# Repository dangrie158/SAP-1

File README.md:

# SAP-1 (Simple as Possible)

A simple 8-bit micro-processor using mostly discrete logic chips.

This project is mostly based on the [8-bit Breadboard computer](https://eater.net/8bit) by [Ben Eater](https://eater.net)

## Banner Specs

- ~400 Hz Clock
- 8-bit Data Bus
- 16-bit Control Word
- 5 Microsteps per Instruction
- 16 byte RAM

## Documentation

Check the projects [Pages](https://dangrie158.github.io/SAP-1/) for the documentation of the ISA and Hardware modules.

## Submodules:

- Clock with adjustable frequency and single-step button
- 2 8-bit Data Registers (A & B)
- ALU implementing sum and difference between Registers A & B, carry and zero flag
- Flag Register to save the ALU flags between instructions
- 4-bit Instruction Counter with load (jump)
- Output module to display a byte as positive decimal or 2s-complement with data latch
- Random Access Memory with 16 Bytes for instructions and data
- 4-bit Memory Address Register to address the 16 bytes of RAM
- 8-bit Instruction Register with the upper nibble representing the opcode, the lower nibble can be used for instruction parameters
- Instruction Decoder to run the microcode of the 16 different instructions with 5 microinstuctions each. Uses a 16-bit control word to control the other modules

## Project Structure

| Files                           | Description                                                                                   |
|---------------------------------|-----------------------------------------------------------------------------------------------|
| ```Board/Board.*```             | Autodesk Eagle project woth the Schematic and a fully routed Boardlayout                      |
| ```Board/Board_*.zip```         | precreated Gerbers for Production                                                             |
| ```Board/BOM.xlsx```            | a BOM with [Mouser](https://www.mouser.com) partnumbers                                       |
| ```Spec/ISA.py```               | a Python module that defines and documents the Instruction Set Architecture of the Processor. |
| ```Spec/lut_microcode.py```     | script to create the microcode LUT binary for the ID EEPROMS. Uses ```ISA.py```               |
| ```Spec/lut_outputdecoder.py``` | script to create the LUT binary for the output decode EEPROM                                  |
| ```LUTs/*.bin```                | precreated binaries for the EEPROMS                                                           |
| ```Example-Programs/*.s```      | Some Example Programs in SAP-1 assembly                                                       |
| ```Tools/sap-asm```             | Assembler for SAP-1 assembly listings. Outputs binaries or prints programming instructions.   |
| ```Simulations/```              | [iCircuit](http://icircuitapp.com) simulation files for some parts of the architecture        |

## Writing Code
The documentation has an extensive section on the [Instruction Set Architecture](https://dangrie158.github.io/SAP-1/isa.html) you can use to get started writing programs.

### Assembler:

In the ``Tools`` directory an assembler is available that can either output binary files or, if it detects stdout to be a TTY, prints programming instructions for you to manually program the RAM using the DIP-Switches.

```
$ cat Example-Programs/Counter.s 
.data:
0xF: 0x1

LDA 0xF
loop:
OUT
ADD 0xF
JMP loop

$ Tools/sap-asm Example-Programs/Counter.s
○○○○: ○○○●●●●●
○○○●: ●●●○○○○○
○○●○: ○○●○●●●●
○○●●: ○●●○○○○●
●●●●: ○○○○○○○●

$ Tools/sap-asm Example-Programs/Counter.s | hexdump 
0000000 1f e0 2f 61 00 00 00 00 00 00 00 00 00 00 00 01
0000010
```

## Programming the EEPROM LUTs

The provided ```Makefile``` offers some convenient rules to create the LUTs and program them to an EEPROM.
To program the LUTs you can use an [Arduino based programmer](https://github.com/dangrie158/EEPROgraMmer)
with only 2 external chips (+EEPROM) which is the officially supported method using the 
[```eepro```](https://pypi.org/project/eepro/) CLI. 

However, you can also use any other programmer to flash the binary files created by the scripts.

If you want to use ```eepro```, make sure the package is installed

```bash
pip3 install -r requirements.txt
```

Then you can programm the needed 3 EEPROMS (1x Output Decoder, 2x Microcode) using 

```bash
make program_lut file=LUTs/microcode.bin        # < for the microcode EEPROMS
make program_lut file=LUTs/outputdecoder.bin    # < for the Output Decoder EEPROM
```

The rule makes sure the LUTs are created or updated if the creating script has changed since last creation.

If you want to use any other programmer, just run 

```bash
make luts
```

to create the binaries in the ```LUTs/``` directory.

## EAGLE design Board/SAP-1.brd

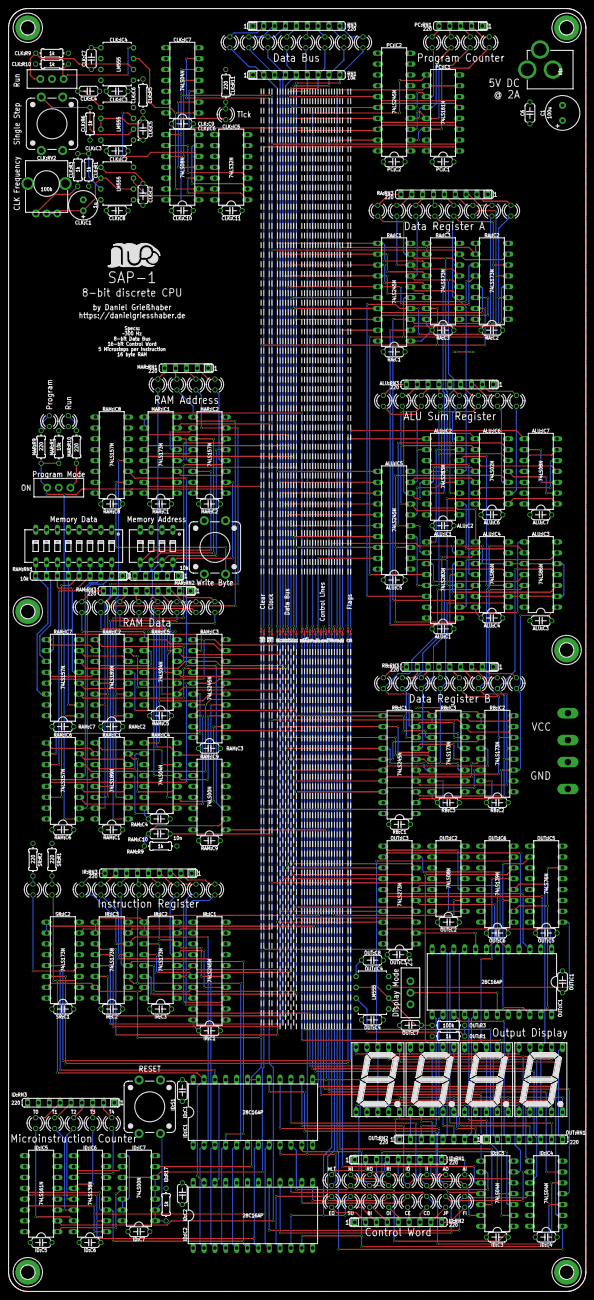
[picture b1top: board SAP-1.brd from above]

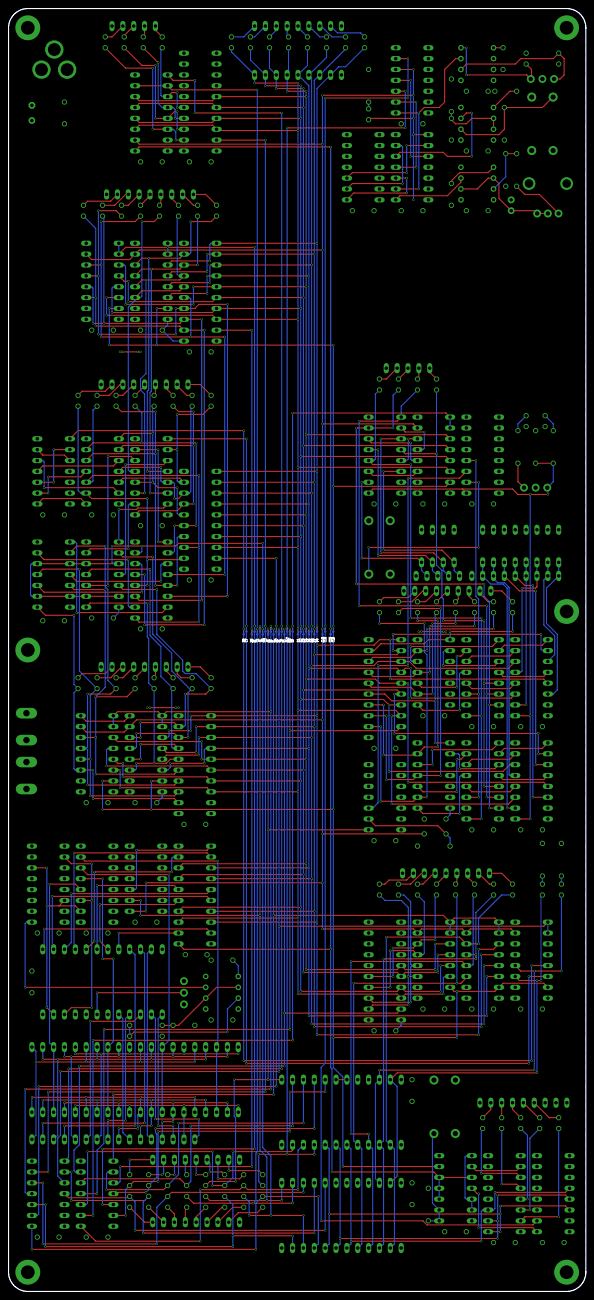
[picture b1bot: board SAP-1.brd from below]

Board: 2 copper layers, 135.0 x 300.0 mm, 305 parts (30 on the bottom side), 294 nets.

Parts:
ALU:C1, ALU:C2, ALU:C3, ALU:C4, ALU:C5, ALU:C6, ALU:C7: 100n; C050-024X044
ALU:IC1, ALU:IC2: 74LS283N; DIL16
ALU:IC3, ALU:IC4: 74LS86N; DIL14
ALU:IC5: 74LS245N; DIL20
ALU:IC6: 74LS02N; DIL14
ALU:IC7: 74LS08N; DIL14
ALU:LED1, ALU:LED2, ALU:LED3, ALU:LED4, ALU:LED5, ALU:LED6, ALU:LED7, ALU:LED8: RED; LED3MM
ALU:RN3: 220; SIL9
C1: 100u; E3,5-8
C6: 100n; C050-024X044
CLK:C1: 1u; E2,5-7
CLK:C2, CLK:C3, CLK:C4, CLK:C5, CLK:C6, CLK:C7, CLK:C8, CLK:C9, CLK:C10, CLK:C11: 100n; C050-024X044
CLK:IC2, CLK:IC3, CLK:IC4: LM555; DIP8
CLK:IC5: 74LS32N; DIL14
CLK:IC6: 74LS08N; DIL14
CLK:IC7: 74LS04N; DIL14
CLK:LED1: RED; LED3MM
CLK:R1, CLK:R3, CLK:R6, CLK:R9, CLK:R10: 1k; 0204/7
CLK:R5: 1M; 0204/7
CLK:R11: 220; 0204/7
CLK:RV2: 100k; ALPS_POT_KIT
CLK:S1: Single Step; TACTILE_SWITCH_PTH_12MM
CLK:S2: Source Select; SWITCH_SPDT_PTH_11.6X4.0MM_KIT
CLK:TP1, CLK:TP2, CLK:TP3, CLK:TP4: TPTP06R; TP06R
H1, H2, H3, H4: MOUNT-PAD-ROUND3.2; 3,2-PAD
H5, H6: 3.2; 3,2-PAD
ID:AI: RED; LED3MM
ID:AO: RED; LED3MM
ID:BI: RED; LED3MM
ID:C1, ID:C2, ID:C3, ID:C4, ID:C5, ID:C6, ID:C7: 100n; C050-024X044
ID:CE: RED; LED3MM
ID:CO: RED; LED3MM
ID:EO: RED; LED3MM
ID:FI: RED; LED3MM
ID:HLT: RED; LED3MM
ID:IC1, ID:IC2: 28C16AP; DIL24-6
ID:IC3, ID:IC4: 74LS04N; DIL14
ID:IC5: 74LS161N; DIL16
ID:IC6: 74LS138N; DIL16
ID:IC7: 74LS00N; DIL14
ID:II: RED; LED3MM
ID:IO: RED; LED3MM
ID:JP: RED; LED3MM
ID:MI: RED; LED3MM
ID:OI: RED; LED3MM
ID:R17: 1k; 0204/7
ID:RI: RED; LED3MM
ID:RN1, ID:RN2, ID:RN3: 220; SIL9
ID:RO: RED; LED3MM
ID:S1: Reset; TACTILE_SWITCH_PTH_12MM
ID:SU: RED; LED3MM
ID:T0, ID:T1, ID:T2, ID:T3, ID:T4: GREEN; LED3MM
ID:TP1, ID:TP2, ID:TP3, ID:TP4, ID:TP5, ID:TP6, ID:TP7, ID:TP8, ID:TP9, ID:TP10, ID:TP11, ID:TP12, ID:TP13, ID:TP14, ID:TP15, ID:TP16, ID:TP17, ID:TP18, ID:TP19, ID:TP20, ID:TP21, ID:TP22, ID:TP23, ID:TP24, ID:TP25, ID:TP26, ID:TP27, ID:TP28, ID:TP29, ID:TP30, ID:TP31, ID:TP32, ID:TP33, ID:TP34, ID:TP35, ID:TP36: TPTP06R; TP06R
IR:C1, IR:C2, IR:C3: 100n; C050-024X044
IR:IC1: 74LS245N; DIL20
IR:IC2, IR:IC3: 74LS173N; DIL16
IR:LED1, IR:LED2, IR:LED3, IR:LED4: RED; LED3MM
IR:LED5, IR:LED6, IR:LED7, IR:LED8: BLUE; LED3MM
IR:RN3: 220; SIL9
J1, J2: TERMINAL-1BRIDGE; VOGT-1098A.68
LED1, LED2, LED3, LED4, LED5, LED6, LED7, LED8: RED; LED3MM
MAR:C1, MAR:C2: 100n; C050-024X044
MAR:IC1: 74LS173N; DIL16
MAR:IC2: 74LS157N; DIL16
MAR:LED1, MAR:LED2, MAR:LED3, MAR:LED4: BLUE; LED3MM
MAR:PROG: RED; LED3MM
MAR:R1: 10k; 0204/7
MAR:R9, MAR:R10: 220; 0204/7
MAR:RN1: 220; SIL5
MAR:RN2: 10k; SIL5
MAR:RUN: GREEN; LED3MM
MAR:S1: Memory Address; DIP04YL
MAR:S3: Program / Write; SWITCH_SPDT_PTH_11.6X4.0MM_KIT
OUT:C1, OUT:C2, OUT:C3, OUT:C4, OUT:C5, OUT:C6, OUT:C8: 100n; C050-024X044
OUT:C7: 10n; C050-024X044
OUT:D1, OUT:D2, OUT:D3, OUT:D4: RED; 7SEG-13
OUT:IC1: 28C16AP; DIL24-6
OUT:IC2: 74LS08N; DIL14
OUT:IC3: 74LS273N; DIL20
OUT:IC4: LM555; DIP8
OUT:IC5: 74LS76N; DIL16
OUT:IC6: 74LS139N; DIL16
OUT:R1: 1k; 0204/7
OUT:R3: 100k; 0204/7
OUT:RN1, OUT:RN2: 220; SIL8
OUT:S3: 2's Complement; SWITCH_SPDT_PTH_11.6X4.0MM_KIT
PC:C1, PC:C2: 100n; C050-024X044
PC:IC1: 74LS161N; DIL16
PC:IC2: 74LS245N; DIL20
PC:LED1, PC:LED2, PC:LED3, PC:LED4: BLUE; LED3MM
PC:RN1: 220; SIL5
RA:C1, RA:C2, RA:C3: 100n; C050-024X044
RA:IC1: 74LS245N; DIL20
RA:IC2, RA:IC3: 74LS173N; DIL16
RA:LED1, RA:LED2, RA:LED3, RA:LED4, RA:LED5, RA:LED6, RA:LED7, RA:LED8: RED; LED3MM
RA:RN3: 220; SIL9
RAM:C1, RAM:C2, RAM:C3, RAM:C4, RAM:C5, RAM:C6, RAM:C7, RAM:C8, RAM:C9: 100n; C050-024X044
RAM:C10: 10n; C050-024X044
RAM:IC1, RAM:IC2: 74LS189N; DIL16
RAM:IC3: 74LS245N; DIL20
RAM:IC4, RAM:IC5: 74LS04N; DIL14
RAM:IC6, RAM:IC7, RAM:IC8: 74LS157N; DIL16
RAM:IC9: 74LS00N; DIL14
RAM:LED1, RAM:LED2, RAM:LED3, RAM:LED4, RAM:LED5, RAM:LED6, RAM:LED7, RAM:LED8: RED; LED3MM
RAM:R9: 1k; 0204/7
RAM:RN1: 10k; SIL9
RAM:RN3: 220; SIL9
RAM:S1: Write Byte; TACTILE_SWITCH_PTH_12MM
RAM:S2: Memory Data; DIP08YL
RB:C1, RB:C2, RB:C3: 100n; C050-024X044
RB:IC1: 74LS245N; DIL20
RB:IC2, RB:IC3: 74LS173N; DIL16
RB:LED1, RB:LED2, RB:LED3, RB:LED4, RB:LED5, RB:LED6, RB:LED7, RB:LED8: RED; LED3MM
RB:RN3: 220; SIL9
RN1: 10k; SIL9
RN3: 220; SIL9
SR:C1: 100n; C050-024X044
SR:IC2: 74LS173N; DIL16
SR:LED1, SR:LED2: BLUE; LED3MM
SR:R1, SR:R2: 220; 0204/7
SR:TP1, SR:TP2, SR:TP3, SR:TP4: TPTP06R; TP06R
TP1, TP2, TP3, TP4, TP5, TP6, TP7, TP8, TP9, TP10, TP11, TP12, TP13, TP14, TP15, TP16: TPTP06R; TP06R
U$1: DC-JACK; POWER_JACK_PTH
U$2: LOGO-SILKSCREEN

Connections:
!AI: ID:IC3.12, ID:TP8.TP, ID:TP26.TP, RA:IC2.9, RA:IC2.10, RA:IC3.9, RA:IC3.10
!AO: ID:IC3.10, ID:TP7.TP, ID:TP25.TP, RA:IC1.19
!BI: ID:IC4.4, ID:TP11.TP, ID:TP29.TP, RB:IC2.9, RB:IC2.10, RB:IC3.9, RB:IC3.10
!CLK: CLK:IC7.6, CLK:TP1.TP, CLK:TP4.TP, ID:IC5.2
!CLR: ID:IC7.3, ID:IC7.4, ID:IC7.5, ID:IC7.10, ID:TP18.TP, ID:TP35.TP, OUT:IC3.1, PC:IC1.1
!CO: ID:IC4.6, ID:TP14.TP, ID:TP32.TP, PC:IC2.19
!EO: ALU:IC5.19, ID:IC4.2, ID:TP9.TP, ID:TP27.TP
!FI: ID:IC4.10, ID:TP16.TP, ID:TP34.TP, SR:IC2.9, SR:IC2.10
!II: ID:IC3.8, ID:TP6.TP, ID:TP24.TP, IR:IC2.9, IR:IC2.10, IR:IC3.9, IR:IC3.10
!IO: ID:IC3.6, ID:TP5.TP, ID:TP23.TP, IR:IC1.19
!JP: ID:IC4.8, ID:TP15.TP, ID:TP33.TP, PC:IC1.9
!MI: ID:IC3.2, ID:TP2.TP, ID:TP20.TP, MAR:IC1.9, MAR:IC1.10
!RO: ID:IC3.4, ID:TP3.TP, ID:TP21.TP, RAM:IC3.19
ALU:N$1: ALU:IC1.9, ALU:IC2.7
ALU:N$2: ALU:IC6.1, ALU:IC7.1
ALU:N$3: ALU:IC6.4, ALU:IC7.2
ALU:N$4: ALU:IC6.10, ALU:IC7.4
ALU:N$5: ALU:IC6.13, ALU:IC7.5
ALU:N$6: ALU:IC7.3, ALU:IC7.9
ALU:N$7: ALU:IC7.6, ALU:IC7.10
ALU:N$8: ALU:LED8.K, ALU:RN3.9
ALU:N$9: ALU:LED7.K, ALU:RN3.8
ALU:N$10: ALU:LED6.K, ALU:RN3.7
ALU:N$11: ALU:LED5.K, ALU:RN3.6
ALU:N$12: ALU:LED4.K, ALU:RN3.5
ALU:N$13: ALU:LED3.K, ALU:RN3.4
ALU:N$14: ALU:LED2.K, ALU:RN3.3
ALU:N$15: ALU:LED1.K, ALU:RN3.2
ALU:N$18: ALU:IC1.6, ALU:IC3.3
ALU:N$19: ALU:IC1.2, ALU:IC3.6
ALU:N$20: ALU:IC1.15, ALU:IC3.8
ALU:N$21: ALU:IC1.11, ALU:IC3.11
ALU:N$22: ALU:IC2.6, ALU:IC4.3
ALU:N$23: ALU:IC2.2, ALU:IC4.6
ALU:N$24: ALU:IC2.15, ALU:IC4.8
ALU:N$25: ALU:IC2.11, ALU:IC4.11
ALU:S1: ALU:IC1.4, ALU:IC5.2, ALU:IC6.2, ALU:LED1.A
ALU:S2: ALU:IC1.1, ALU:IC5.3, ALU:IC6.3, ALU:LED2.A
ALU:S3: ALU:IC1.13, ALU:IC5.4, ALU:IC6.5, ALU:LED3.A
ALU:S4: ALU:IC1.10, ALU:IC5.5, ALU:IC6.6, ALU:LED4.A
ALU:S5: ALU:IC2.4, ALU:IC5.6, ALU:IC6.8, ALU:LED5.A
ALU:S6: ALU:IC2.1, ALU:IC5.7, ALU:IC6.9, ALU:LED6.A
ALU:S7: ALU:IC2.13, ALU:IC5.8, ALU:IC6.11, ALU:LED7.A
ALU:S8: ALU:IC2.10, ALU:IC5.9, ALU:IC6.12, ALU:LED8.A
CE: ID:CE.A, ID:IC2.14, ID:TP13.TP, ID:TP31.TP, PC:IC1.7, PC:IC1.10
CF: ID:IC1.23, ID:IC2.23, SR:IC2.3, SR:LED2.A
CLK: CLK:IC6.8, CLK:IC7.5, CLK:LED1.A, CLK:TP2.TP, CLK:TP3.TP, IR:IC2.7, IR:IC3.7, MAR:IC1.7, OUT:IC2.1, PC:IC1.2, RA:IC2.7, RA:IC3.7, RAM:C10.1, RB:IC2.7, RB:IC3.7, SR:IC2.7
CLK:CLK_SEL: CLK:IC4.3, CLK:IC6.2, CLK:IC7.1
CLK:CLK_STEP: CLK:IC3.3, CLK:IC6.5
CLK:CLK_TICK: CLK:IC2.3, CLK:IC6.1
CLK:N$1: CLK:C1.+, CLK:IC2.2, CLK:IC2.6, CLK:RV2.P$2, CLK:RV2.P$3
CLK:N$2: CLK:IC2.7, CLK:R1.1, CLK:R3.2
CLK:N$3: CLK:R3.1, CLK:RV2.P$1
CLK:N$4: CLK:LED1.K, CLK:R11.2
CLK:N$6: CLK:C2.1, CLK:IC2.5
CLK:N$7: CLK:IC3.2, CLK:R6.1, CLK:S1.3
CLK:N$8: CLK:C4.1, CLK:IC3.5
CLK:N$11: CLK:C5.1, CLK:IC3.6, CLK:IC3.7, CLK:R5.1
CLK:N$12: CLK:C7.1, CLK:IC4.5
CLK:N$13: CLK:IC6.4, CLK:IC7.2
CLK:N$14: CLK:IC5.1, CLK:IC6.3
CLK:N$15: CLK:IC4.2, CLK:R9.1, CLK:S2.1
CLK:N$16: CLK:IC4.4, CLK:R10.1, CLK:S2.3
CLK:N$17: CLK:IC5.2, CLK:IC6.6
CLK:N$18: CLK:IC5.3, CLK:IC6.9
CLK:N$19: CLK:IC6.10, CLK:IC7.4
CLR: ID:IC7.6, ID:TP17.TP, ID:TP36.TP, IR:IC2.15, IR:IC3.15, MAR:IC1.15, RA:IC2.15, RA:IC3.15, RB:IC2.15, RB:IC3.15, SR:IC2.15
CY: ALU:IC2.9, SR:IC2.14, SR:TP1.TP, SR:TP4.TP
D1: ALU:IC5.18, IR:IC1.18, IR:IC2.14, LED1.A, MAR:IC1.14, OUT:IC3.3, PC:IC1.3, PC:IC2.18, RA:IC1.18, RA:IC2.14, RAM:IC3.18, RAM:IC6.3, RB:IC1.18, RB:IC2.14, RN1.9, TP8.TP, TP16.TP
D2: ALU:IC5.17, IR:IC1.17, IR:IC2.13, LED2.A, MAR:IC1.13, OUT:IC3.4, PC:IC1.4, PC:IC2.17, RA:IC1.17, RA:IC2.13, RAM:IC3.17, RAM:IC6.6, RB:IC1.17, RB:IC2.13, RN1.8, TP7.TP, TP15.TP
D3: ALU:IC5.16, IR:IC1.16, IR:IC2.12, LED3.A, MAR:IC1.12, OUT:IC3.7, PC:IC1.5, PC:IC2.16, RA:IC1.16, RA:IC2.12, RAM:IC3.16, RAM:IC6.10, RB:IC1.16, RB:IC2.12, RN1.7, TP6.TP, TP14.TP
D4: ALU:IC5.15, IR:IC1.15, IR:IC2.11, LED4.A, MAR:IC1.11, OUT:IC3.8, PC:IC1.6, PC:IC2.15, RA:IC1.15, RA:IC2.11, RAM:IC3.15, RAM:IC6.13, RB:IC1.15, RB:IC2.11, RN1.6, TP5.TP, TP13.TP
D5: ALU:IC5.14, IR:IC3.14, LED5.A, OUT:IC3.13, RA:IC1.14, RA:IC3.14, RAM:IC3.14, RAM:IC7.3, RB:IC1.14, RB:IC3.14, RN1.5, TP4.TP, TP12.TP
D6: ALU:IC5.13, IR:IC3.13, LED6.A, OUT:IC3.14, RA:IC1.13, RA:IC3.13, RAM:IC3.13, RAM:IC7.6, RB:IC1.13, RB:IC3.13, RN1.4, TP3.TP, TP11.TP
D7: ALU:IC5.12, IR:IC3.12, LED7.A, OUT:IC3.17, RA:IC1.12, RA:IC3.12, RAM:IC3.12, RAM:IC7.10, RB:IC1.12, RB:IC3.12, RN1.3, TP2.TP, TP10.TP
D8: ALU:IC5.11, IR:IC3.11, LED8.A, OUT:IC3.18, RA:IC1.11, RA:IC3.11, RAM:IC3.11, RAM:IC7.13, RB:IC1.11, RB:IC3.11, RN1.2, TP1.TP, TP9.TP
GND: ALU:C1.2, ALU:C2.2, ALU:C3.2, ALU:C4.2, ALU:C5.2, ALU:C6.2, ALU:C7.2, ALU:IC1.8, ALU:IC2.8, ALU:IC3.7, ALU:IC4.7, ALU:IC5.10, ALU:IC6.7, ALU:IC7.7, ALU:IC7.12, ALU:IC7.13, ALU:RN3.1, C1.-, C6.2, CLK:C1.-, CLK:C2.2, CLK:C3.2, CLK:C4.2, CLK:C5.2, CLK:C6.2, CLK:C7.2, CLK:C8.2, CLK:C9.2, CLK:C10.2, CLK:C11.2, CLK:IC2.1, CLK:IC3.1, CLK:IC4.1, CLK:IC4.6, CLK:IC4.7, CLK:IC5.4, CLK:IC5.5, CLK:IC5.7, CLK:IC5.9, CLK:IC5.10, CLK:IC5.12, CLK:IC5.13, CLK:IC6.7, CLK:IC6.12, CLK:IC6.13, CLK:IC7.7, CLK:IC7.9, CLK:IC7.11, CLK:IC7.13, CLK:R11.1, CLK:S1.1, CLK:S2.2, H1.B3,2, H2.B3,2, H3.B3,2, H4.B3,2, H5.B3,2, H6.B3,2, ID:C1.2, ID:C2.2, ID:C3.2, ID:C4.2, ID:C5.2, ID:C6.2, ID:C7.2, ID:IC1.1, ID:IC1.12, ID:IC1.18, ID:IC1.19, ID:IC1.20, ID:IC2.12, ID:IC2.18, ID:IC2.19, ID:IC2.20, ID:IC3.7, ID:IC4.7, ID:IC4.13, ID:IC5.3, ID:IC5.4, ID:IC5.5, ID:IC5.6, ID:IC5.8, ID:IC6.4, ID:IC6.5, ID:IC6.8, ID:IC7.7, ID:R17.1, ID:RN1.1, ID:RN2.1, ID:RN3.1, IR:C1.2, IR:C2.2, IR:C3.2, IR:IC1.6, IR:IC1.7, IR:IC1.8, IR:IC1.9, IR:IC1.10, IR:IC2.1, IR:IC2.2, IR:IC2.8, IR:IC3.1, IR:IC3.2, IR:IC3.8, IR:RN3.1, J2.P$1, J2.P$2, MAR:C1.2, MAR:C2.2, MAR:IC1.1, MAR:IC1.2, MAR:IC1.8, MAR:IC2.8, MAR:IC2.15, MAR:RN1.1, MAR:S1.1, MAR:S1.2, MAR:S1.3, MAR:S1.4, MAR:S3.2, OUT:C1.2, OUT:C2.2, OUT:C3.2, OUT:C4.2, OUT:C5.2, OUT:C6.2, OUT:C7.2, OUT:C8.2, OUT:IC1.12, OUT:IC1.18, OUT:IC1.20, OUT:IC2.4, OUT:IC2.5, OUT:IC2.7, OUT:IC2.9, OUT:IC2.10, OUT:IC2.12, OUT:IC2.13, OUT:IC3.10, OUT:IC4.1, OUT:IC5.13, OUT:IC6.1, OUT:IC6.8, OUT:IC6.13, OUT:IC6.14, OUT:S3.1, PC:C1.2, PC:C2.2, PC:IC1.8, PC:IC2.6, PC:IC2.7, PC:IC2.8, PC:IC2.9, PC:IC2.10, PC:RN1.1, RA:C1.2, RA:C2.2, RA:C3.2, RA:IC1.10, RA:IC2.1, RA:IC2.2, RA:IC2.8, RA:IC3.1, RA:IC3.2, RA:IC3.8, RA:RN3.1, RAM:C1.2, RAM:C2.2, RAM:C3.2, RAM:C4.2, RAM:C5.2, RAM:C6.2, RAM:C7.2, RAM:C8.2, RAM:C9.2, RAM:IC1.2, RAM:IC1.8, RAM:IC2.2, RAM:IC2.8, RAM:IC3.10, RAM:IC4.7, RAM:IC4.11, RAM:IC4.13, RAM:IC5.7, RAM:IC5.11, RAM:IC5.13, RAM:IC6.8, RAM:IC6.15, RAM:IC7.8, RAM:IC7.15, RAM:IC8.5, RAM:IC8.6, RAM:IC8.8, RAM:IC8.10, RAM:IC8.11, RAM:IC8.13, RAM:IC8.14, RAM:IC8.15, RAM:IC9.4, RAM:IC9.5, RAM:IC9.7, RAM:IC9.9, RAM:IC9.10, RAM:IC9.12, RAM:IC9.13, RAM:R9.1, RAM:RN3.1, RAM:S1.1, RAM:S2.1, RAM:S2.2, RAM:S2.3, RAM:S2.4, RAM:S2.5, RAM:S2.6, RAM:S2.7, RAM:S2.8, RB:C1.2, RB:C2.2, RB:C3.2, RB:IC1.10, RB:IC2.1, RB:IC2.2, RB:IC2.8, RB:IC3.1, RB:IC3.2, RB:IC3.8, RB:RN3.1, RN1.1, RN3.1, SR:C1.2, SR:IC2.1, SR:IC2.2, SR:IC2.8, SR:IC2.11, SR:IC2.12, SR:R1.1, SR:R2.1, U$1.GND, U$1.GNDBREAK
HLT: CLK:IC7.3, ID:HLT.A, ID:IC1.9, ID:TP1.TP, ID:TP19.TP
ID:!T0: ID:IC6.15, ID:T0.A
ID:!T1: ID:IC6.14, ID:T1.A
ID:!T2: ID:IC6.13, ID:T2.A
ID:!T3: ID:IC6.12, ID:T3.A
ID:!T4: ID:IC6.11, ID:T4.A
ID:AI: ID:AI.A, ID:IC1.17, ID:IC3.13
ID:AO: ID:AO.A, ID:IC1.16, ID:IC3.11
ID:BI: ID:BI.A, ID:IC2.11, ID:IC4.3
ID:CO: ID:CO.A, ID:IC2.15, ID:IC4.5
ID:EO: ID:EO.A, ID:IC2.9, ID:IC4.1
ID:FI: ID:FI.A, ID:IC2.17, ID:IC4.11
ID:II: ID:IC1.15, ID:IC3.9, ID:II.A
ID:IO: ID:IC1.14, ID:IC3.5, ID:IO.A
ID:JP: ID:IC2.16, ID:IC4.9, ID:JP.A
ID:MI: ID:IC1.10, ID:IC3.1, ID:MI.A
ID:MI1: ID:IC1.8, ID:IC2.8, ID:IC5.14, ID:IC6.1
ID:MI2: ID:IC1.7, ID:IC2.7, ID:IC5.13, ID:IC6.2
ID:MI3: ID:IC1.6, ID:IC2.6, ID:IC5.12, ID:IC6.3
ID:N$1: ID:HLT.K, ID:RN1.2
ID:N$2: ID:MI.K, ID:RN1.3
ID:N$3: ID:RN1.4, ID:RO.K
ID:N$4: ID:RI.K, ID:RN1.5
ID:N$5: ID:IO.K, ID:RN1.6
ID:N$6: ID:II.K, ID:RN1.7
ID:N$7: ID:AO.K, ID:RN1.8
ID:N$8: ID:AI.K, ID:RN1.9
ID:N$9: ID:EO.K, ID:RN2.2
ID:N$10: ID:RN2.3, ID:SU.K
ID:N$11: ID:BI.K, ID:RN2.4
ID:N$12: ID:OI.K, ID:RN2.5
ID:N$13: ID:CE.K, ID:RN2.6
ID:N$14: ID:CO.K, ID:RN2.7
ID:N$15: ID:JP.K, ID:RN2.8
ID:N$16: ID:IC7.1, ID:IC7.2, ID:R17.2, ID:S1.3
ID:N$17: ID:IC5.1, ID:IC7.11
ID:N$18: ID:IC7.8, ID:IC7.12, ID:IC7.13
ID:N$19: ID:IC6.10, ID:IC7.9
ID:N$31: ID:FI.K, ID:RN2.9
ID:N$33: ID:RN3.4, ID:T2.K
ID:N$34: ID:RN3.2, ID:T4.K
ID:N$35: ID:RN3.3, ID:T3.K
ID:N$36: ID:RN3.5, ID:T1.K
ID:N$37: ID:RN3.6, ID:T0.K
ID:RO: ID:IC1.11, ID:IC3.3, ID:RO.A
IR:B1: IR:IC1.2, IR:IC2.3, IR:LED1.A
IR:B2: IR:IC1.3, IR:IC2.4, IR:LED2.A
IR:B3: IR:IC1.4, IR:IC2.5, IR:LED3.A
IR:B4: IR:IC1.5, IR:IC2.6, IR:LED4.A
IR:N$1: IR:LED8.K, IR:RN3.9
IR:N$2: IR:LED7.K, IR:RN3.8
IR:N$3: IR:LED6.K, IR:RN3.7
IR:N$5: IR:LED5.K, IR:RN3.6
IR:N$6: IR:LED4.K, IR:RN3.5
IR:N$7: IR:LED3.K, IR:RN3.4
IR:N$8: IR:LED2.K, IR:RN3.3
IR:N$9: IR:LED1.K, IR:RN3.2
MAR:I5: MAR:IC1.3, MAR:IC2.3
MAR:I6: MAR:IC1.4, MAR:IC2.6
MAR:I7: MAR:IC1.5, MAR:IC2.10
MAR:I8: MAR:IC1.6, MAR:IC2.13
MAR:N$1: MAR:IC2.2, MAR:RN2.2, MAR:S1.8
MAR:N$2: MAR:LED4.K, MAR:RN1.5
MAR:N$3: MAR:IC2.5, MAR:RN2.3, MAR:S1.7
MAR:N$4: MAR:LED3.K, MAR:RN1.4
MAR:N$5: MAR:IC2.11, MAR:RN2.4, MAR:S1.6
MAR:N$7: MAR:R10.2, MAR:S3.3
MAR:N$8: MAR:LED2.K, MAR:RN1.3
MAR:N$9: MAR:PROG.K, MAR:R9.1
MAR:N$10: MAR:LED1.K, MAR:RN1.2
MAR:N$11: MAR:IC2.14, MAR:RN2.5, MAR:S1.5
MAR:N$13: MAR:R10.1, MAR:RUN.K
unnamed: ALU:IC2.12, RA:IC1.9, RA:IC3.6, RA:LED8.A
unnamed: ALU:IC2.14, RA:IC1.8, RA:IC3.5, RA:LED7.A
unnamed: ALU:IC2.3, RA:IC1.7, RA:IC3.4, RA:LED6.A
unnamed: ALU:IC2.5, RA:IC1.6, RA:IC3.3, RA:LED5.A
unnamed: ALU:IC1.12, RA:IC1.5, RA:IC2.6, RA:LED4.A
unnamed: ALU:IC1.14, RA:IC1.4, RA:IC2.5, RA:LED3.A
unnamed: ALU:IC1.3, RA:IC1.3, RA:IC2.4, RA:LED2.A
unnamed: ALU:IC1.5, RA:IC1.2, RA:IC2.3, RA:LED1.A
unnamed: ALU:IC3.1, RB:IC1.2, RB:IC2.3, RB:LED1.A
unnamed: ALU:IC3.4, RB:IC1.3, RB:IC2.4, RB:LED2.A
unnamed: ALU:IC3.9, RB:IC1.4, RB:IC2.5, RB:LED3.A
unnamed: ALU:IC3.12, RB:IC1.5, RB:IC2.6, RB:LED4.A
unnamed: ALU:IC4.1, RB:IC1.6, RB:IC3.3, RB:LED5.A
unnamed: ALU:IC4.4, RB:IC1.7, RB:IC3.4, RB:LED6.A
unnamed: ALU:IC4.9, RB:IC1.8, RB:IC3.5, RB:LED7.A
unnamed: ALU:IC4.12, RB:IC1.9, RB:IC3.6, RB:LED8.A
unnamed: MAR:IC2.4, MAR:LED1.A, RAM:IC1.1, RAM:IC2.1
unnamed: MAR:IC2.7, MAR:LED2.A, RAM:IC1.15, RAM:IC2.15
unnamed: MAR:IC2.9, MAR:LED3.A, RAM:IC1.14, RAM:IC2.14
unnamed: MAR:IC2.12, MAR:LED4.A, RAM:IC1.13, RAM:IC2.13
unnamed: MAR:IC2.1, MAR:R1.2, MAR:R9.2, MAR:S3.1, RAM:IC6.1, RAM:IC7.1, RAM:IC8.1
unnamed: LED8.K, RN3.2
unnamed: LED7.K, RN3.3
unnamed: LED6.K, RN3.4
unnamed: LED5.K, RN3.5
unnamed: LED4.K, RN3.6
unnamed: LED3.K, RN3.7
unnamed: LED2.K, RN3.8
unnamed: LED1.K, RN3.9
unnamed: ID:IC1.5, ID:IC2.5, IR:IC3.3, IR:LED5.A
unnamed: ID:IC1.4, ID:IC2.4, IR:IC3.4, IR:LED6.A
unnamed: ID:IC1.3, ID:IC2.3, IR:IC3.5, IR:LED7.A
unnamed: ID:IC1.2, ID:IC2.2, IR:IC3.6, IR:LED8.A
OI: ID:IC2.13, ID:OI.A, ID:TP12.TP, ID:TP30.TP, OUT:IC2.2
OUT:2SC: OUT:IC1.19, OUT:S3.2
OUT:DIG1: OUT:D1.3, OUT:D1.8, OUT:IC6.4
OUT:DIG2: OUT:D2.3, OUT:D2.8, OUT:IC6.5
OUT:DIG3: OUT:D3.3, OUT:D3.8, OUT:IC6.6
OUT:DIG4: OUT:D4.3, OUT:D4.8, OUT:IC6.7
OUT:DISP_CLK: OUT:IC4.3, OUT:IC5.1
OUT:DS1: OUT:IC1.23, OUT:IC5.6, OUT:IC5.14, OUT:IC6.2
OUT:DS2: OUT:IC1.22, OUT:IC5.10, OUT:IC6.3
OUT:N$1: OUT:IC1.8, OUT:IC3.2
OUT:N$2: OUT:IC1.7, OUT:IC3.5
OUT:N$3: OUT:IC1.6, OUT:IC3.6
OUT:N$4: OUT:IC1.5, OUT:IC3.9
OUT:N$5: OUT:IC1.4, OUT:IC3.12
OUT:N$6: OUT:IC1.3, OUT:IC3.15
OUT:N$7: OUT:IC1.2, OUT:IC3.16
OUT:N$8: OUT:IC1.1, OUT:IC3.19
OUT:N$9: OUT:IC2.3, OUT:IC3.11
OUT:N$10: OUT:C7.1, OUT:IC4.2, OUT:IC4.6, OUT:R3.1
OUT:N$13: OUT:IC4.7, OUT:R1.1, OUT:R3.2
OUT:N$15: OUT:C8.1, OUT:IC4.5
OUT:N$17: OUT:IC1.14, OUT:RN2.1
OUT:SEG_A: OUT:D1.7, OUT:D2.7, OUT:D3.7, OUT:D4.7, OUT:RN1.6
OUT:SEG_AO: OUT:IC1.9, OUT:RN1.5
OUT:SEG_B: OUT:D1.6, OUT:D2.6, OUT:D3.6, OUT:D4.6, OUT:RN1.8
OUT:SEG_BO: OUT:IC1.10, OUT:RN1.7
OUT:SEG_C: OUT:D1.4, OUT:D2.4, OUT:D3.4, OUT:D4.4, OUT:RN2.6
OUT:SEG_CO: OUT:IC1.11, OUT:RN2.5
OUT:SEG_D: OUT:D1.2, OUT:D2.2, OUT:D3.2, OUT:D4.2, OUT:RN2.4
OUT:SEG_DO: OUT:IC1.13, OUT:RN2.3
OUT:SEG_DP: OUT:D1.5, OUT:D2.5, OUT:D3.5, OUT:D4.5, OUT:RN2.8
OUT:SEG_DPO: OUT:IC1.17, OUT:RN2.7
OUT:SEG_E: OUT:D1.1, OUT:D2.1, OUT:D3.1, OUT:D4.1, OUT:RN2.2
OUT:SEG_F: OUT:D1.9, OUT:D2.9, OUT:D3.9, OUT:D4.9, OUT:RN1.4
OUT:SEG_FO: OUT:IC1.15, OUT:RN1.3
OUT:SEG_G: OUT:D1.10, OUT:D2.10, OUT:D3.10, OUT:D4.10, OUT:RN1.2
OUT:SEG_GO: OUT:IC1.16, OUT:RN1.1
PC:N$1: PC:LED4.K, PC:RN1.5
PC:N$2: PC:LED3.K, PC:RN1.4
PC:N$3: PC:LED2.K, PC:RN1.3
PC:N$4: PC:LED1.K, PC:RN1.2
PC:Q1: PC:IC1.14, PC:IC2.2, PC:LED1.A
PC:Q2: PC:IC1.13, PC:IC2.3, PC:LED2.A
PC:Q3: PC:IC1.12, PC:IC2.4, PC:LED3.A
PC:Q4: PC:IC1.11, PC:IC2.5, PC:LED4.A
RA:N$1: RA:LED1.K, RA:RN3.2
RA:N$2: RA:LED2.K, RA:RN3.3
RA:N$3: RA:LED3.K, RA:RN3.4
RA:N$4: RA:LED4.K, RA:RN3.5
RA:N$5: RA:LED5.K, RA:RN3.6
RA:N$6: RA:LED6.K, RA:RN3.7
RA:N$7: RA:LED7.K, RA:RN3.8
RA:N$8: RA:LED8.K, RA:RN3.9
RAM:!WRITE: RAM:IC1.3, RAM:IC2.3, RAM:IC8.4
RAM:B1: RAM:IC1.4, RAM:IC6.4
RAM:B2: RAM:IC1.6, RAM:IC6.7
RAM:B3: RAM:IC1.10, RAM:IC6.9
RAM:B4: RAM:IC1.12, RAM:IC6.12
RAM:B5: RAM:IC2.4, RAM:IC7.4
RAM:B6: RAM:IC2.6, RAM:IC7.7
RAM:B7: RAM:IC2.10, RAM:IC7.9
RAM:B8: RAM:IC2.12, RAM:IC7.12
RAM:I1: RAM:IC3.2, RAM:IC4.2, RAM:LED1.A
RAM:I2: RAM:IC3.3, RAM:IC4.4, RAM:LED2.A
RAM:I3: RAM:IC3.4, RAM:IC4.6, RAM:LED3.A
RAM:I4: RAM:IC3.5, RAM:IC4.8, RAM:LED4.A
RAM:I5: RAM:IC3.6, RAM:IC5.2, RAM:LED5.A
RAM:I6: RAM:IC3.7, RAM:IC5.4, RAM:LED6.A
RAM:I7: RAM:IC3.8, RAM:IC5.6, RAM:LED7.A
RAM:I8: RAM:IC3.9, RAM:IC5.8, RAM:LED8.A
RAM:N$1: RAM:IC1.5, RAM:IC4.1
RAM:N$2: RAM:IC1.7, RAM:IC4.3
RAM:N$3: RAM:IC1.9, RAM:IC4.5
RAM:N$4: RAM:IC1.11, RAM:IC4.9
RAM:N$5: RAM:IC2.5, RAM:IC5.1
RAM:N$6: RAM:IC2.7, RAM:IC5.3
RAM:N$7: RAM:IC2.9, RAM:IC5.5
RAM:N$8: RAM:IC2.11, RAM:IC5.9
RAM:N$9: RAM:LED8.K, RAM:RN3.9
RAM:N$10: RAM:LED7.K, RAM:RN3.8
RAM:N$11: RAM:LED6.K, RAM:RN3.7
RAM:N$12: RAM:LED5.K, RAM:RN3.6
RAM:N$13: RAM:LED4.K, RAM:RN3.5
RAM:N$14: RAM:LED3.K, RAM:RN3.4
RAM:N$15: RAM:LED2.K, RAM:RN3.3
RAM:N$16: RAM:LED1.K, RAM:RN3.2
RAM:N$17: RAM:IC8.2, RAM:S1.3
RAM:N$18: RAM:IC7.14, RAM:RN1.9, RAM:S2.9
RAM:N$19: RAM:IC7.11, RAM:RN1.8, RAM:S2.10
RAM:N$20: RAM:IC7.5, RAM:RN1.7, RAM:S2.11
RAM:N$21: RAM:IC7.2, RAM:RN1.6, RAM:S2.12
RAM:N$22: RAM:IC6.14, RAM:RN1.5, RAM:S2.13
RAM:N$23: RAM:IC6.11, RAM:RN1.4, RAM:S2.14
RAM:N$24: RAM:IC6.5, RAM:RN1.3, RAM:S2.15
RAM:N$25: RAM:IC6.2, RAM:RN1.2, RAM:S2.16
RAM:N$26: RAM:IC8.3, RAM:IC9.3
RAM:N$27: RAM:C10.2, RAM:IC9.2, RAM:R9.2
RB:N$1: RB:LED8.K, RB:RN3.9
RB:N$2: RB:LED7.K, RB:RN3.8
RB:N$3: RB:LED6.K, RB:RN3.7
RB:N$4: RB:LED5.K, RB:RN3.6
RB:N$5: RB:LED4.K, RB:RN3.5
RB:N$6: RB:LED3.K, RB:RN3.4
RB:N$7: RB:LED2.K, RB:RN3.3
RB:N$8: RB:LED1.K, RB:RN3.2
RI: ID:IC1.13, ID:RI.A, ID:TP4.TP, ID:TP22.TP, RAM:IC9.1
SR:N$1: SR:LED1.K, SR:R2.2
SR:N$2: SR:LED2.K, SR:R1.2
SU: ALU:IC1.7, ALU:IC3.2, ALU:IC3.5, ALU:IC3.10, ALU:IC3.13, ALU:IC4.2, ALU:IC4.5, ALU:IC4.10, ALU:IC4.13, ID:IC2.10, ID:SU.A, ID:TP10.TP, ID:TP28.TP
VCC: ALU:C1.1, ALU:C2.1, ALU:C3.1, ALU:C4.1, ALU:C5.1, ALU:C6.1, ALU:C7.1, ALU:IC1.16, ALU:IC2.16, ALU:IC3.14, ALU:IC4.14, ALU:IC5.1, ALU:IC5.20, ALU:IC6.14, ALU:IC7.14, C1.+, C6.1, CLK:C3.1, CLK:C6.1, CLK:C8.1, CLK:C9.1, CLK:C10.1, CLK:C11.1, CLK:IC2.4, CLK:IC2.8, CLK:IC3.4, CLK:IC3.8, CLK:IC4.8, CLK:IC5.14, CLK:IC6.14, CLK:IC7.14, CLK:R1.2, CLK:R5.2, CLK:R6.2, CLK:R9.2, CLK:R10.2, ID:C1.1, ID:C2.1, ID:C3.1, ID:C4.1, ID:C5.1, ID:C6.1, ID:C7.1, ID:IC1.21, ID:IC1.24, ID:IC2.1, ID:IC2.21, ID:IC2.24, ID:IC3.14, ID:IC4.14, ID:IC5.7, ID:IC5.9, ID:IC5.10, ID:IC5.16, ID:IC6.6, ID:IC6.16, ID:IC7.14, ID:S1.1, IR:C1.1, IR:C2.1, IR:C3.1, IR:IC1.1, IR:IC1.20, IR:IC2.16, IR:IC3.16, J1.P$1, J1.P$2, MAR:C1.1, MAR:C2.1, MAR:IC1.16, MAR:IC2.16, MAR:PROG.A, MAR:R1.1, MAR:RN2.1, MAR:RUN.A, OUT:C1.1, OUT:C2.1, OUT:C3.1, OUT:C4.1, OUT:C5.1, OUT:C6.1, OUT:IC1.21, OUT:IC1.24, OUT:IC2.14, OUT:IC3.20, OUT:IC4.4, OUT:IC4.8, OUT:IC5.2, OUT:IC5.3, OUT:IC5.4, OUT:IC5.5, OUT:IC5.7, OUT:IC5.8, OUT:IC5.9, OUT:IC5.12, OUT:IC5.16, OUT:IC6.15, OUT:IC6.16, OUT:R1.2, OUT:S3.3, PC:C1.1, PC:C2.1, PC:IC1.16, PC:IC2.1, PC:IC2.20, RA:C1.1, RA:C2.1, RA:C3.1, RA:IC1.1, RA:IC1.20, RA:IC2.16, RA:IC3.16, RAM:C1.1, RAM:C2.1, RAM:C3.1, RAM:C4.1, RAM:C5.1, RAM:C6.1, RAM:C7.1, RAM:C8.1, RAM:C9.1, RAM:IC1.16, RAM:IC2.16, RAM:IC3.1, RAM:IC3.20, RAM:IC4.14, RAM:IC5.14, RAM:IC6.16, RAM:IC7.16, RAM:IC8.16, RAM:IC9.14, RAM:RN1.1, RB:C1.1, RB:C2.1, RB:C3.1, RB:IC1.1, RB:IC1.20, RB:IC2.16, RB:IC3.16, SR:C1.1, SR:IC2.16, U$1.PWR
ZF: ID:IC1.22, ID:IC2.22, SR:IC2.4, SR:LED1.A
ZR: ALU:IC7.8, SR:IC2.13, SR:TP2.TP, SR:TP3.TP

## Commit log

2019-07-13 added first functional modules to schematic
2019-07-13 Started first layout blocks of the board
2019-07-13 added gitignore
2019-07-13 Added simulation of clock circuit
2019-07-13 added RAM module and MAR
2019-07-13 added program counter
2019-07-13 added output module
2019-07-13 connected seperate modules
2019-07-13 added instruction decoder module
2019-07-13 added CPU status register
2019-07-14 added current limiting resistors
2019-07-14 added mouser part numbers
2019-07-14 added BOM
2019-07-15 layed out components on board
2019-07-15 replace most discrete resistors with networks
2019-07-16 started routing of modules
2019-07-17 routed seperate modules except power nets
2019-07-18 added first routing pass
2019-07-18 added mounting holes
2019-07-18 rounded board outline
2019-07-18 first silkscreen cleanup pass and labeling
2019-07-19 Second Silkscreen cleanup pass
2019-08-04 updated attributes of resistor networks
2019-08-04 added script to create output decoder LUT
2019-08-04 added py virtual env managed by direnv
2019-08-04 added script to create microcode LUT
2019-08-04 added production gerbers
2019-08-04 added pregenerated LUTs
2019-08-04 added makefile for LUT creation and programming
2019-08-04 added README
2019-08-04 updated BOM part numbers
2019-08-06 fixed minor issues with silkscreen
2019-08-06 added block diagram image for documentation
2019-08-07 fixed wrong segment in number 9 in output LUT
2019-08-07 switched to sphinx for documentation
2019-08-07 moved docs directory for github pages
2019-08-09 written most of the documentation for the submodules
2019-08-09 built documentation from sources
2019-08-09 updated prebuild output LUT
2019-08-09 fixed silkscreen error
2019-08-09 updated documentation link to docu
2019-08-10 lowered value of reset pull down
2019-08-10 removed buffering of instruction register upper nibble
2019-08-11 fixed wrong active segments for 4 and 6 in output decoder LUT
2019-08-11 added simple assembler for SAP-1 ISA
2019-08-11 added section aboud writing programs and the assembler
2019-08-11 added title page to docs
2019-08-11 added image of processor to readme
2019-08-11 added overview image to docs
2019-08-11 added image to generated docs
2019-08-11 resized overview image
2019-08-12 improved error reporting of SyntaxErrors
2019-08-12 added second example program
2019-08-14 added first code of emulator
2019-08-14 added flags register module
2019-08-16 refactored bus and signal creation
2019-08-16 added missing ram chip 74LS161
2019-08-16 added logic gate SN74LS00
2019-08-16 added 1 of 8 decocer 74LS138
2019-08-16 modified project structure to allow relative package imports
2019-08-16 added function to render a 7-segment display using the termional
2019-08-17 refactored ISA Spec file
2019-08-17 refactored ISA Spec
2019-08-17 added all modules to emulator
2019-08-18 improved file loading for assembler finding files relative for the CWD
2019-08-18 refactored main architecture to supoort program loading
2019-08-20 fixed naming of has_parameter flag
2019-08-20 added mypy cache to gitignore
2019-08-20 added basic ncurses based visualisation to emulator
2019-08-20 improved emulator visualization
2019-08-20 added disassembly view to emulator
2019-08-20 added emulator info and controls info to emulator display
2019-08-21 added clock halting when control line is high
2019-08-21 added key handling and argument parsing
2019-08-21 fixed clock notification in single step mode
2019-08-21 set initial clock source to single step
2020-01-14 updated emulator code
2020-01-14 fixed issue #5 where the flag bit positions were flipped
2020-01-14 added section about drive current of output decoder rto docs to address #3
2020-01-14 updated gerbers to reflect latest PCB changes, fixes #2
2020-01-14 fixed partnumber of CLK:IC7 (74LS06->74LLS04) to fix #1
2022-08-09 licence the project under the MIT domain
2022-10-25 fixed use of deprecated clock.time function

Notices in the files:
parts and their libraries:
SparkFun-Switches: Licensing: Creative Commons ShareAlike 4.0 International - https://creativecommons.org/licenses/by-sa/4.0
